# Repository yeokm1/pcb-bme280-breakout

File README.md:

# pcb-bme280-breakout
Pin breakout of the Bosch BME280 sensor to through-hole pin headers for prototyping

##PCB Design software and addons used

1. Eagle 7.4.0: I use Standard but Light should still be able to open/modify the files.
2. BME280 object from [Sparkfun](https://github.com/sparkfun/SparkFun_BME280_Breakout_Board)

##Images
None at this time

##Schematic drawings
Images are exported from Eagle at 600dpi.

##Parts required

The BME280 can be bought from one of the online stores like [Mouser](http://www.mouser.sg/new/bosch-sensortec/bosch-bme280/)

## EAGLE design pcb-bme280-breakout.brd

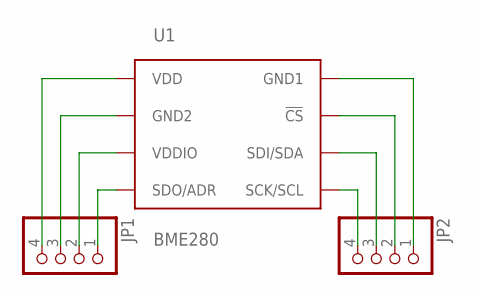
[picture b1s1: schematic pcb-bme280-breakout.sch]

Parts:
JP1, JP2: PINHD-1X4; 1X04
U1: BME280; BME280_LGA

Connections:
unnamed: JP1.4, U1.P$8 (VDD)
unnamed: JP1.3, U1.P$7 (GND2)
unnamed: JP1.2, U1.P$6 (VDDIO)
unnamed: JP1.1, U1.P$5 (SDO/ADR)
unnamed: JP2.4, U1.P$4 (SCK/SCL)
unnamed: JP2.3, U1.P$3 (SDI/SDA)
unnamed: JP2.2, U1.P$2 (!CS)
unnamed: JP2.1, U1.P$1 (GND1)

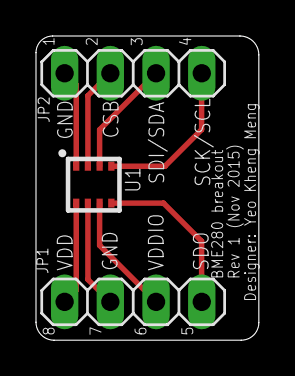
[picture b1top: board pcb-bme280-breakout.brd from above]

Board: 2 copper layers, 12.4 x 16.9 mm, 3 parts (0 on the bottom side), 8 nets.

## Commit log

2015-11-14 mitre corners
2015-11-14 rev1 gerbel
2015-11-14 images
